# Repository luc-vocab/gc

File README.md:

Grind Control Device
====================

**2025/05/25 update: please see this new project https://github.com/LollosoSi/bruxism-detector**

**2015/10/01 update: I've started a new project, a wearable device focused on tracking sleep bruxism: 
 <a href="https://sleeptrack.io">SleepTrack</a>**

<b>Disclaimer: use this design, or any of the parts at your own risk.</b>

This device attemps to prevent night-time bruxism. It works by detecting muscle activation on the temporalis 
muscle and will emit an audio signal to wake the user up if bruxism is detected.

Features:
* Has an audio jack to plug-in headphones. These headphones are use to play an audio tone that will wake up the user during sleep if grinding is detected.
* An [EMG circuit](http://www.advancertechnologies.com/) is used along with custom-made electrodes that are placed on the temporalis muscle.
* A micro-SD card is used to record bruxism patterns for later analysis.
* A custom-made case was designed which can be 3d-printed.

The design is heavily inspired by the commercially available [Grind Care](http://grindcare.com/) device (which appears to no longer be available), except an audio signal is used instead of electrical impulses.

Do you have questions ? You may want to read all of the info below. You can also [contact me](mailto:grindcontrol@mailc.net)

Similar Projects
----------------
* Peter is planning on launching a commercial device, called Grindbit http://grindbit.launchrock.com/ - http://community.particle.io/t/im-building-a-night-time-bruxism-sleep-tracking-wearable-device/16840/6?u=dustpuppy
* Anthony is building a similar device, using a LIPO battery, an OLED display, SRAM chips http://chompr.blogspot.com
* Frank is starting on a similar project http://forums.adafruit.com/viewtopic.php?f=8&t=25611
* Lucy built a device using the EMG sensor and wrote a research paper http://lucyaimeemorcos.wordpress.com/2013/12/17/dont-grind-your-gears-pictures/
* Anthony setup a mailing list to discuss bruxism detection / prevention projects: https://groups.google.com/d/forum/bruxhackers

Photos
======

The device is worn around the neck, held by a strap:

Three electrodes are stuck on the temporalis muscle, the red one on the middle of the muscle, the blue one at the end, and the black one at a neutral area of the skin. Earphones are used for the audio signal:

The device with strap, earphone, and electrode cable. The case is a custom designed enclosure, designed in Sketchup and printed using Selective Laser Sintering:

Inside of the device, with two 9V batteries:

The printed circuit board. You can see the Arduino Micro microcontroller, micro-sd card reader, muscle sensor, switches and 3.5mm headphone jack.

The printed circuit board, designed in Eagle:

Schematics in Eagle:

Parts List
==========
* **Adafruit Arduino Micro** https://www.adafruit.com/products/1086
* **Adafruit MicroSD breakout board** https://www.adafruit.com/products/254
* **Advancer Technologies Muscle Sensor V3** http://www.advancertechnologies.com/p/muscle-sensor-v3.html
  * Also comes with electrodes
* **SS12SDH2 switch** http://www.mouser.hk/Search/ProductDetail.aspx?R=SS12SDH2virtualkey63300000virtualkey633-SS12SDH2
  * this switch is used to register an alarm / cancel the permanent alarm once it goes off.
* **SS22SDH2 switch** http://www.mouser.hk/Search/ProductDetail.aspx?R=SS22SDH2virtualkey63300000virtualkey633-SS22SDH2
  * this switch is used to power on the device. It simultaneously connects the two batteries.
* **66WR1KLF potentiometer / trimmer resistor** http://www.mouser.hk/Search/ProductDetail.aspx?R=66WR1KLFvirtualkey57700000virtualkey858-66WR1KLF
  * used to control the volume in the headphones
* **35RAPC2BV4 3.5mm headphone jack** http://www.mouser.hk/Search/ProductDetail.aspx?R=35RAPC2BV4virtualkey50210000virtualkey502-35RAPC2BV4
  * for audio output into headphones
* **10k ohm resistor**, a standard resistor will do.
* **MicroSD card** any capacity will do, the device usually outputs a 1mb file per night
* **MicroSD card reader** the data has to be analyzed on your computer using a card reader
* **Printed Circuit Board**, designed in Eagle CAD and printed using http://www.seeedstudio.com (https://github.com/lucwastiaux/gc/tree/master/gc1_eagle_project)
* **3d-printed case** printed using http://www.sculpteo.com, white SLS print (https://github.com/lucwastiaux/gc/tree/master/case)
* **9V batteries** http://www.amazon.com/gp/product/B0051WZ516 , these need to have enough capacity to last a whole night, the 550mah seem to last through a whole 10hr night. 
  * order enough of them as they are completely drained after one night
* **9V battery charger** http://www.amazon.com/gp/product/B005PUZQ04
* **2x 9V connectors + wires*** any electronics stores will have those
* **Rubber band** to hold the case together
* **Shure SE215 headphones** http://www.shure.com/americas/products/earphones/se-earphones/se215-sound-isolating-earphones
  * in-ear headphones with decent volume, and stay inside the ears the whole night.
* **Strapworks 1" tubular polyester webbing, 2 ft** http://www.strapworks.com/product_p/stpw1.htm
  * this is the hollow nylon strap used to wrap the headphone cable, electrode cable, and support strap
* **Strapworks 3/4" 4ft adjustable strap** http://www.strapworks.com/Strap_Adjuster_Straps_p/sas34l.htm
  * support strap to hold the device around the neck
 
Building
========

PCB
---
The PCB can be order on http://www.seeedstudio.com/. Select **Fusion PCB** service 
* PCB Qty. - 5 ( you can order more if you want to play around but the minimum is 5)
* Layer - 2
* PCB Thickness - 1.6mm
* PCB Dimension - 10cm Max*10cm Max
* PCB Color - Green
* Surface Finish - Hasl
* E-Test - 100% E-test(Free)

Submit the following zip file: https://github.com/lucwastiaux/gc/blob/master/gc1_eagle_project/gerber/gc1_20130428.zip

This should get you the exact same PCB that I have on my device without requiring processing in Eagle CAD. You will have 5 PCBs, and I recommend dedicating one for testing. You can solder male/female headers on that one to easily add/remove the Arduino, microSD breakout, and muscle sensor (other components like switches, you can just order extra and solder them on directly).

History and development
=======================

Symptoms and Diagnosis
----------------------
In October 2010, I started experiencing an unexplained permanent dizziness. It would come and go and be more severe 
during certain weeks. By March 2011, the symptoms had become more severe and included permanent headaches and facial
muscle pain. I started making doctor's appointments, saw three neurologists, one ENT doctor, took blood samples, had an
MRI brain scan but no diagnosis yet. Since the beginning I had been researching an explanation for those symptoms on the
web. Many leads did not pan out but I read that night-time bruxism (unconscious grinding of teeth at night-time) could
be a possible explanations. Several things pointed in that direction:
* I had been told before that I grind my teeth at night.
* My symptoms started one month after the end of an orthodontic treatment. After my orthodontic appliance was removed, I had to wear an Invisalign appliance, which is a transparent plastic mold designed to keep your teeth in place.
* Very quickly after starting to wear the Invisalign appliance, it started to show wear marks at the points of contact of my teeth.

I made an appointment with a New York dentist who made a special mouth guard designed to fit on the front teeth only.
This had a hugely positive impact on my symptoms and two months after wearing that, I believed the problem was gone.

However I occasionally still felt dizziness. In October of 2011, I had ocasional dizziness and semi-permanent headaches again.
This time, I experienced pain when chewing which clearly pointed to an issue with the jaw and especially jaw muscles.
In march 2012, I went to see a dentist in Hong Kong who made another type of mouthguard, and eventually put tooth fillings on my back teeth
to attempt to remediate a malocclusion problem. This had a beneficial impact. The dentist mentioned that night-time
bruxism is extremely challenging to control, that it may be caused by stress, but may become habitual and persist even
after the stress stimulus is removed.

In September 2012, I purchased the Grind Care device which detects night-time bruxism and attemps to condition you out of 
it by triggering a small electric shock. It's a very well made very compact device which you wear at night around your neck.
At electrode is stuck on your face near the temporal muscle. The electrode serves both to monitor muscle activity and
send a shock if muscle contraction is detected.

The grindcare device was the thing that helped me the most up to that point. It would give me some metrics of how many times
I ground my teeth at night. It started out at 140/night, then progressively moved to 30/night. My symptoms improved radically.
However by December 2012 the number of grinds/night started increasing, to 100/night, 200/night and even as high as 300/night
, as if my body had somehow adjusted and no longer cared about the electric shock.

The idea started forming in my head that the device should not just send an electric shock, but actually wake me up if 
bruxism is detected.

Development of Grind Control Device
-----------------------------------

In December 2012, I purchased a book on electronics to refresh my knowledge on the topic and learn some of the necessary
techniques such as soldering. I experimented with an USB voltmeter capable of detecting +/- 200mV. I started experimenting
with Operational Amplifiers. However in order to accurately detect muscle activity, you need a true EMG signal processing circuit.
I purchased an Olimex EMG and Arduino kit. That kit turned out not to be sensitive enough to detect temporal muscle activity.
A couple of weeks later, I received my Advancer Technologies Muscle Sensor v3. Through playing around with the electrodes
connected on my face, and measuring output voltage with a multimeter, I realized this was the way to go. The output voltage would
show 0.1V with muscles relaxed, and +0.9V with muscles contracted. This was perfect and exactly within the range that I needed
to process the signal with my Arduino Micro.

I needed some other parts in addition to the EMG sensor and Arduino Micro. In order to study grinding patterns, I needed
to record data and hence got the Adafruit microSD adapter. The programming is quite simple if you follow instructions. I also
needed an audio output. The arduino can output a square wave using the PWM output which is loud enough to wake you up. Using
a trimmer/potentiometer, I can control the volume. I needed a 3.5mm audio jack, some switches to turn the device on/off, and
one "control" switch.

My first prototype was made using an Adafruit perma-proto board. It's a PCB with a breadboard-like layout. I moved my parts
on there and connected them using solid core wire, soldered the whole thing together and cut off part of the board with shears.

I bought an enclosure which was the right size and had 2 9V battery compartments. The whole thing was quite bulky but it was ready
to use. I could then start working on the detection algorithm.

Later, I learned how to design PCBs in eagle and designed the layout you see above. It took me a couple of tries before getting
it right. Once I had the PCB and all components soldered on, I learned 3d modelling with Sketchup. Designed a case that
would fit 2 9V batteries, the PCB, and would have openings for the switches and connectors. That was a surprisingly easy
part of the process. The case is 3d-printed using Selective Laser Sintering.

Algorithm
---------

Once I had the final prototype ready, I started on fine-tuning my algorithm. I analyzed the data on the micro-sd card using
python scripts. Every morning, i would wake up and try to detect grinding patterns. The baseline output value from the EMG sensor
would be around 30 in general with no activity. When contracting the muscle, it would go up to 150-200. Sometimes it would stay 
at those high values for minutes during the night, about 1-2 hours after falling asleep. Detecting this high activity was easy,
but there were also times where I would see high values, low values alternating but it clearly didn't look like my jaw was 
at rest during that time. The tradeoffs were, I could set up the algorithm to be very sensitive, but there was a higher
risk of being woken up on a false alarm. Or I could set it up to be more permissive, and I would be unable to detect
certain grinding patterns and not fully solve the problem.

I experimented with many algoritms and ended up settling on a relatively easy one: count the number of "high"
values over the last 10 seconds (sampling 4 times per second). If they exceed 5, go into "alert 1" state, and issue an audio
beep with every new high value. Once the number of high readings exceed 10, issue a higher pitched beep with every new high value.
If they exceed 15, then go into alarm mode and continuously beep until the user resets the device.

Notes about using Arduino Micro
-------------------------------

Working with the Arduino Micro was a good experience overall. The only issue is the limited amount of RAM: 2.5kb. This
is very restrictive. The most annoying issue is that the device will automatically reset if you run out of RAM. It took
me a long time to understand that. Other than that, the Arduino is perfect for this application. The power consumption is
such that I'll go through 2 500mah 9V batteries in one night. Not a big deal since I can recharge them easily.

Experiences using the device
============================

For many months I had grown convinced that the source for my issues is an unconscious night-time behavior of my jaw that 
no one could explain. It seemed obvious to me that if I could detect this and stop it then I would solve my problem.
To me this has been a very successful project. Since I started using the device in April 2013, my symptoms have improved
progressively but very noticeably.

The first times I got woken up by the beeping audio sound were a victory for me as I had finally found an effective
system to put a stop to this destructive unconscious habit. I distintively remember being woken up a few times with 
my jaw clenched and the device beeping into my ears. I had no idea why my jaw was clenched but only after I became more
conscious would I relax my jaw muscles. This was a revelation and yet another proof that my problems were due to night-time,
unconscious bruxism.

There are some drawbacks, the biggest one being interference with your sleep. In my case, it was a lot better to interrupt
my sleep than to let the destructive night-time bruxism keep on happening. However sleep segmentation may have some negative side
effects. Ironically, sleep deprivation may lead to headaches so you need to be careful if you try something like that.

One source of frustration is that bruxism is not well understood by the medical community. Most doctors and dentist will
not be able to help you much besides suggesting mouth guards and other dental treatments. There is a belief that bruxism
is caused by malocclusion or other problems in the mouth. While that may be true, i've also heard dentists say that you could
have perfect teeth and still experience bruxism symptoms. Other people will say it's due to stress. In my personal opinion,
bruxism becomes a habit that is very hard to get rid of. While it may initially be due to stress or dental problems, it will
become a habit that you cannot control.

I now no longer wear the device regularly as my symptoms have improved significantly. I will occasionally wear it if I feel
symptoms coming back. But judging by the last 2 months, it seems like it is possible to have a lasting improvement.

Problems with current design
----------------------------
* No LCD screen. This makes it difficult to experiment with different algorithms as you can't tell what the current reading is.
* Only works off 9V batteries. I end up having to charge a new set every day.
* The sensitivity is based on the EMG readings from my muscles. It may vary from one person to another. Right now the only way to change this is in the code.

Potential improvements
----------------------
* Add small LCD screen to show current readings and accumulated high-readings. This will be useful if the device starts beeping in the middle of the night and you don't know why.
* Add some buttons to configure sensitivity. This would allow a new user to use the device without programming.
* As an alternative to the above, I could use a Low-Energy Bluetooth chip and control the whole thing from an iPhone or Android phone. I have
 no experience with that, but it's an interesting idea. Not sure what it would mean for power consumption, although with on-board storage, I wouldn't need
to keep the bluetooth radio on the whole night, only when the user is configuring the device.
* Run off a LIPO battery. This presents some challenges, as the EMG sensor requires a dual power supply, and with the 2 9V batteries forming a +/- 9V dual supply, the output voltage 
of the EMG sensor moves between 0.1V and 0.9V. This is only a small range of the Arduino's 0V-5V resolution. Maybe my mucles are weak. If I were to use a LIPO battery, I would
have to first use a step-up converter to increase the voltage from 3.7V to 9V, and then create a dual power supply. This is beyond my level of knowledge. There are some ready-made boost
converters you can buy, I may look into those. Then I may need a charging circuit for the LIPO, but again that's beyond my area of expertise.

Interested in using this ?
==========================

In its current state, I cannot recommend using this device to anyone who is not an engineer. You may have to do a lot of 
experimentation to get it work for you, however if your bruxism symptoms are as severe as mine were, I can only encourage 
you to pursue this. I'm not planning on making an updated version right now, but several people have expressed interest.
If you have any ideas around this please contact me.

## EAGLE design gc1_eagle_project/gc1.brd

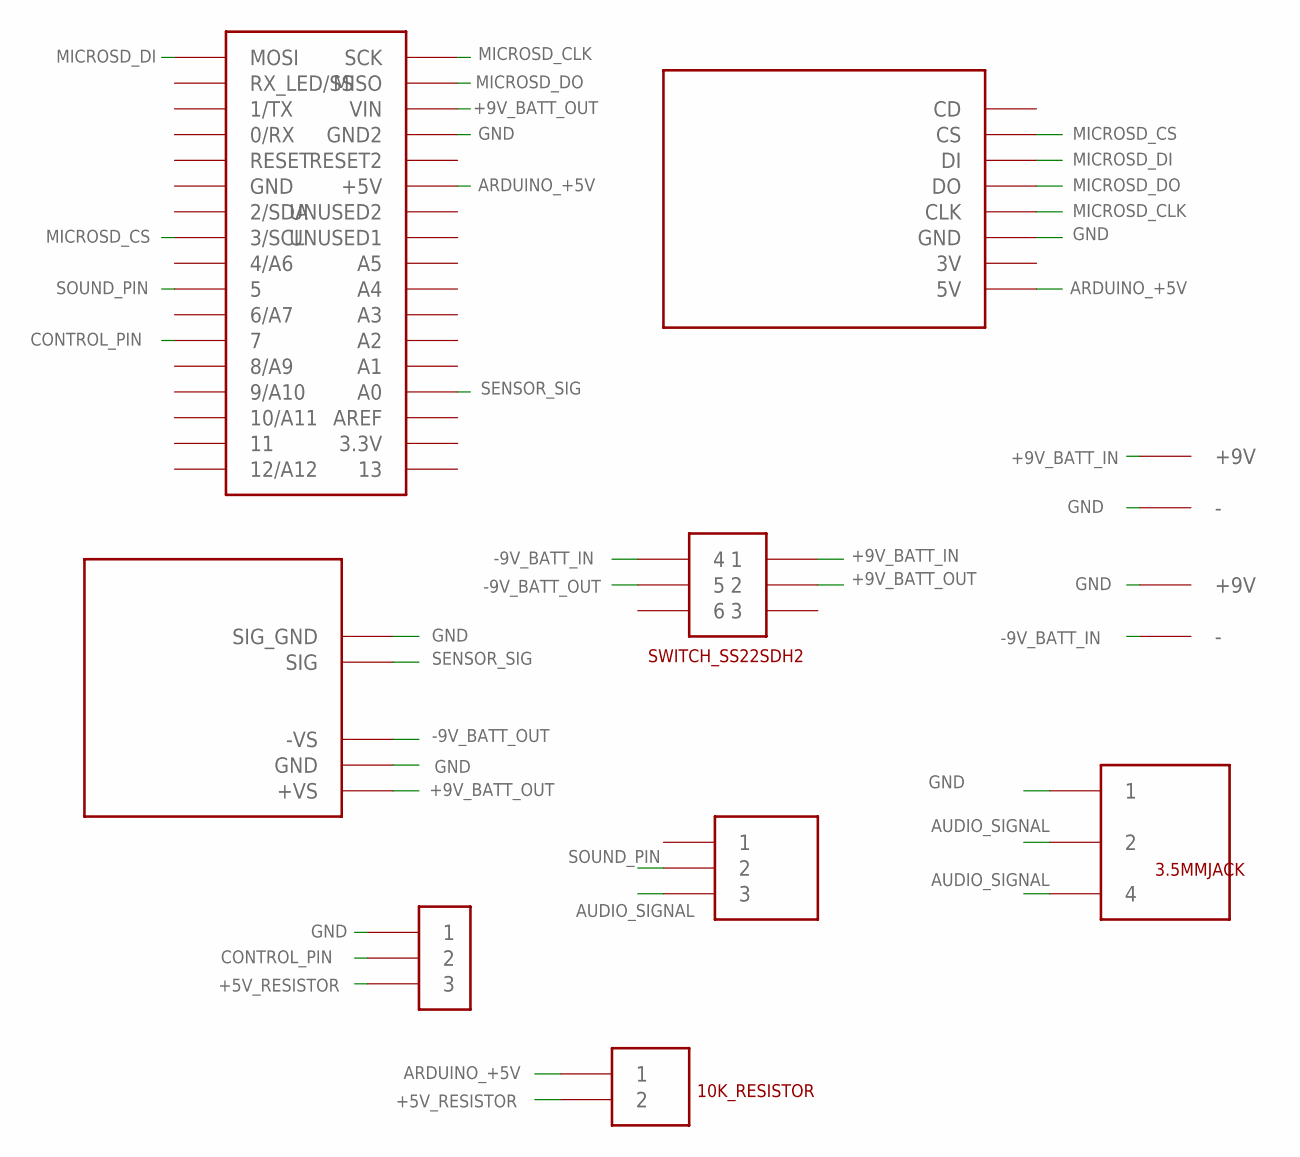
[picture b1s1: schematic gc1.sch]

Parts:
3.5MMJACK: 35RAPC2BVN4; 35RAPC4BVN4
10K_RESISTOR: 10K_RESISTOR
ARDUINOMICRO: ARDUINO_MICRO
TRIMMER: 66WR1KLF
U$2: MICROSD
U$3: MUSCLE_SENSOR
U$4: SWITCH_SS22SDH2
U$5, U$6: 9V_CONNECTOR
U$9: SWITCH_SS12SDH2

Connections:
+5V_RESISTOR: 10K_RESISTOR.2, U$9.3
+9V_BATT_IN: U$4.1, U$5.+9V
+9V_BATT_OUT: ARDUINOMICRO.VIN, U$3.+VS, U$4.2
-9V_BATT_IN: U$4.4, U$6.-
-9V_BATT_OUT: U$3.-VS, U$4.5
ARDUINO_+5V: 10K_RESISTOR.1, ARDUINOMICRO.+5V, U$2.5V
AUDIO_SIGNAL: 3.5MMJACK.2, 3.5MMJACK.4, TRIMMER.3
CONTROL_PIN: ARDUINOMICRO.7, U$9.2
GND: 3.5MMJACK.1, ARDUINOMICRO.GND2, U$2.GND, U$3.GND, U$3.SIG_GND, U$5.-, U$6.+9V, U$9.1
MICROSD_CLK: ARDUINOMICRO.SCK, U$2.CLK
MICROSD_CS: ARDUINOMICRO.3/SCL, U$2.CS
MICROSD_DI: ARDUINOMICRO.MOSI, U$2.DI
MICROSD_DO: ARDUINOMICRO.MISO, U$2.DO
SENSOR_SIG: ARDUINOMICRO.A0, U$3.SIG
SOUND_PIN: ARDUINOMICRO.5, TRIMMER.2

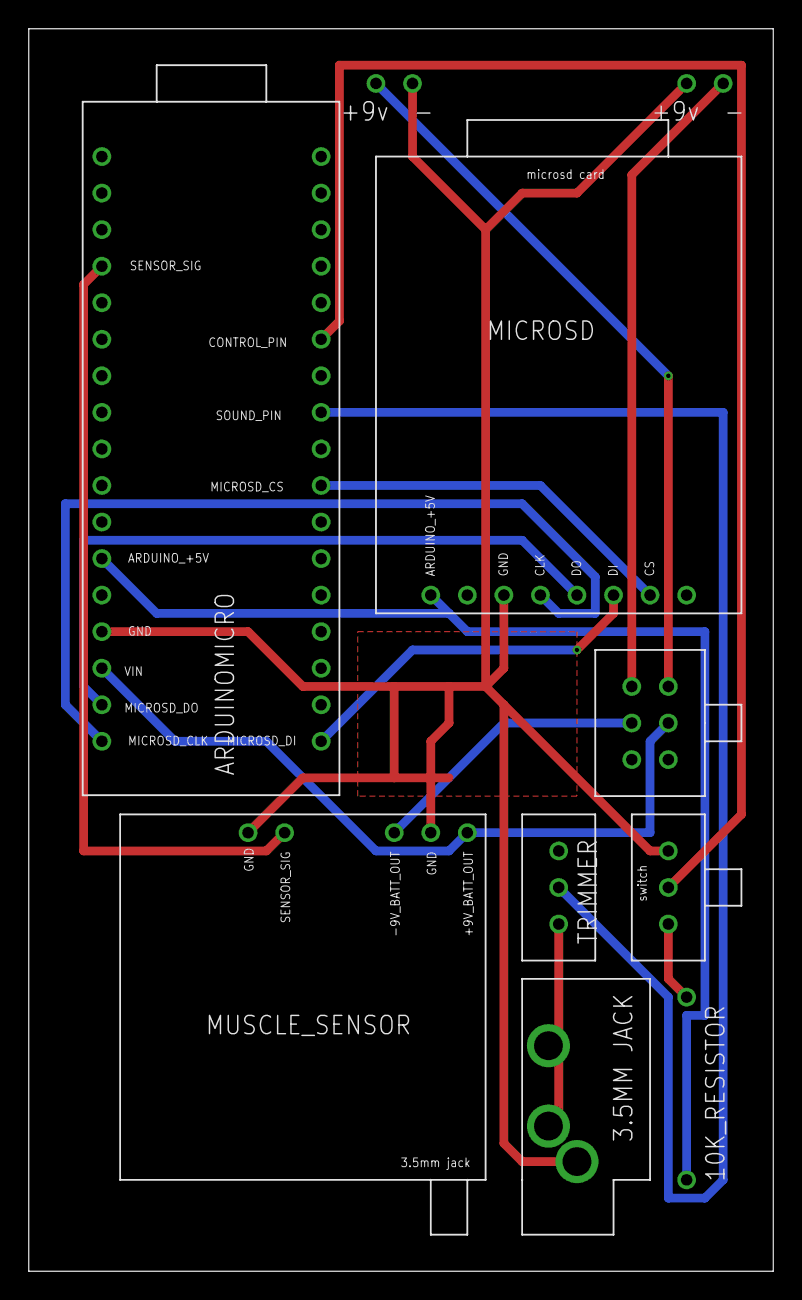
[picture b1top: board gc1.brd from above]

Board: 2 copper layers, 51.7 x 86.4 mm, 10 parts (0 on the bottom side), 15 nets.

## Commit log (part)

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2016-01-17 add log_base function
2016-01-17 remove verbose logging level
2016-01-17 indicate when loading data
2016-01-17 log owner_uid in server, exit test client when done
2016-01-17 support letsencrypt certificate
2016-01-17 allow fetching cloudinary logo over http
2016-01-17 fix image link
2016-01-17 force loading image over https
2016-01-23 server debugging, allow loading multiple gc1 data files, add underscore library
2016-01-23 send confirmation byte after initial handshake
2016-01-23 integrate smoothie charts to show historical emg data
2016-01-23 show min and max values
2016-01-24 disable simulation mode
2016-01-24 report battery level every 2mn
2016-01-26 device monitor to figure out whether device is online or not
2016-01-26 add additional device states, manage routes for control better
2016-01-26 indicate whether device is in realtime mode, don't query influx db unless device is in night mode
2016-01-29 use FB_ROOT as input to gulp config generation
2016-01-30 refactor server code, introduce config class
2016-01-30 use proper environment key in influxdb tags
2016-01-30 remove unneeded config
2016-01-30 add basic docker file
2016-01-30 use common launcher for both servers
2016-01-30 fix selecting different server
2016-01-30 use angular.element instead of jquery
2016-01-30 initial import
2016-01-30 changed date
2016-01-30 include excerpt
2016-01-31 adding necessary css/js files for jekyll
2016-01-31 Housekeeping
    - Removed log files and other misc junk files/
    - uploaded assembly photos for V1
2016-01-31 include font-awesome, add menu entries
2016-01-31 add blog landing page
2016-02-04 remove simple line icons
2016-02-05 remove default sass code, add color function
2016-02-06 moved project status into include file
2016-02-06 fixed update date css
2016-02-06 add blog-specific layout
2016-02-06 adding images
2016-02-06 added more images
2016-02-07 new device article
2016-02-07 add previous/next articles
2016-02-07 improve responisiveness of prev/next articles
2016-02-07 use logo on blog index
2016-02-07 only add padding above a certain width
2016-02-07 use full width below a certain screen size
2016-02-07 use https urls everywhere
2016-02-07 add separate directory for firebase.json for website
2016-02-07 change layout of prev/next post links
2016-02-07 add contact page
2016-02-07 fixed a few links
2016-02-07 added mailmunch form
2016-02-08 sleeptrack link
2016-02-08 fix typo
2016-02-08 put together haptic motor driver test
2016-02-09 change image links to https
2016-02-09 fixed link error
2016-02-14 renamed index.html file, removed assets
2016-02-14 change destination
2016-02-14 build blog on changes
2016-02-14 add fonts back in
2016-02-14 remove spaces in css and js statements
2016-02-14 use absolute path in useref tag
2016-02-14 build blog on gulp build task, put jekyll tasks in separate script
2016-02-14 working redirection to clean urls
2016-02-14 also try adding .html extension to files
2016-02-14 move app.html to app/index.html during inject task
2016-02-14 serve static assets dir as well in dev
2016-02-14 remove blog_site on clean
2016-02-15 add common header sass file
2016-02-15 watch common sass area when building. add padding on either side in mobile mode
2016-02-15 remove pubnub
2016-02-20 in dev mode, generate blog with drafts
2016-02-20 added paragraph about sleepguard advantages
2016-02-21 use new keyword to instantiate new GcInfluxData
2016-02-21 use user_name instead of device_name, as that's the key under which influxdb data gets inserted
2016-02-23 add environment
2016-02-23 add task to copy misc blog files such as feed.xml
2016-02-23 wrote some more on bruxism devices, added email include
2016-02-23 fixed grindcare link
2016-02-23 moved bruxism devices article, added image include
2016-02-23 move google analytics tracker to head
2016-02-25 added two devices
2016-02-27 instantiate device monitor with new
2016-02-27 properly reject promise when saving of settings fails
2016-02-27 watch for changes in user's device_id and update subscription accordingly
2016-02-27 properly show status if no device is configured
2016-02-27 set server key if user already selected one
2016-02-27 show min and max for the 30s and 5s windows
2016-02-27 calculate avg for both time horizons
2016-02-27 imu specs first draft
2016-02-27 first import
2016-02-27 questions
2016-02-27 connector question
2016-02-29 External IMU Board added
    - Updated artwork (Sleeptrack V2 Final)
    -Created IMU External PCB and Schematic
2016-03-01 IMU External PCB Single Sided
    -compressed board to single sided.
    -still need to edit silkscreen and finalize the schematic.
2016-03-02 IMU External
    - Added BOM V1
2016-03-04 IMU External
    -Fixed issue where the copper was not exposed on 0402 components.
    -updated artwork, brd, and schematic pdfs.
2016-03-10 remove simulation mode, change data collection frequency to be slower in realtime mode
2016-03-10 bruxism and rhodiola article
2016-03-10 various edits on magnesium article
2016-03-11 change current status
2016-03-12 bno055 test
2016-03-20 initial myoware model
2016-03-20 added pegs
2016-03-20 few problems left to fix
2016-03-20 sketchup model with only myoware cover
2016-03-20 fixed internal faces in model
2016-03-20 add two more versions
2016-03-21 Housekeeping and documentation updates
    -Added new PDF folder to store Schematic and PCB PDF's
    -cleaned up root
2016-03-21 SleepTrack V3 and IMU External V2 Artwork Generated
    Fixed outstanding issues with the boards and regenerated artwork and
    drill files.
2016-03-21 initial commit of mouthguard bruxism article
2016-03-21 change link to https
2016-03-23 Timesheet 7
    Updated timesheet for 2/29/16-3/22/16
2016-03-24 simulation mode can be toggled
2016-03-24 toggle EMG beep on / off
2016-03-24 remove other gauges
2016-03-25 mark server as connected when reconnection happens
2016-03-25 resize smoothie chart if window in narrow, after taking into account margin
2016-03-25 disable google analytics for anything but prod domain
2016-03-27 elecrow instructions
2016-03-28 SleepTrack V3 Artwork Rev B
    -Updated Artwork to connect USB pin 5 to GND instead of Dummy NEt
    -Removed Vout+ and NC trace
    -Regenerated manufacture files and PDFs
2016-03-30 BRD Git Test
2016-04-09 new article
2016-04-09 added images
2016-04-14 initial commit of first article
2016-04-14 added thumbnails, more paragraphs
2016-04-14 added feaetures left to do
2016-04-15 further clarifications
2016-04-22 Added new circuit components
    -Haptic Feedback
    - BNO055 IMU
2016-04-30 first import of tmj article
2016-05-01 removed unneeded pages, added twitter and facebook contacts
2016-05-01 updated current status (rev 3 of pcb)
2016-05-01 added RSS link
2016-05-01 correctly use active link for blog home
2016-05-04 added components
2016-05-04 pin markings
2016-05-04 added LM3914
2016-05-07 proposed sleeptrack2 design phases
2016-05-07 changed headers
2016-05-07 expose pins with through-holes
2016-05-16 Breakout Board V1
    -Completed Breakout board pcb
    -generated artwork
    - exported pdfs of schematic and pcb
2016-05-16 a few mentions about the circuit
2016-05-21 Directory Change
    -moved all versions of Sleeptrack and Add on boards to Projects Folder
2016-05-30 LM3914 datasheet
2016-05-30 use adafruit BNO055 circuit
2016-06-02 Sleeptrack2_Phase 1 Board Geometry updated
    -added 3 mounting holes (4-40 screw size)
    - filleted corners
2016-06-10 Sleeptrack2_Phase 1
    Final Board Artwork V1
2016-06-10 Revert "Sleeptrack2_Phase 1"
    This reverts commit 92b435aabf790c8d8d8b8fd82f348b68dcef08d7.
2016-06-11 changed phase 2 to include only BNO055
2016-06-11 no need for level switching
2016-06-18 added BNO055 datasheet
2016-06-28 publish charge to particle cloud
2016-07-01 selectable use in IMU in main firmware, publish values on particle cloud in bno055 example
2016-07-01 initial version with texture of board
2016-07-01 working flat board with all component heights
2016-07-01 finished 3d model of case
2016-07-02 initial import of phase1 case
2016-07-02 case and battery space
2016-07-02 finalized top and bottom parts
2016-07-02 working top and bottom cases
2016-07-02 final checkin
2016-07-09 article text
2016-07-09 updated status
2016-07-10 don't attempt to read from IMU if IMU is disabled
2016-07-15 Sleeptrack2 Phase 2 V1
    -Finalized Schematic
    -Finalized PCB
    -Artwork created
    -Drill Files
    -PDF of PCB and Schematic
    Sleeptrack Phase 2 Functions:
2016-07-20 Sleeptrack2_Phase2_v1
    Added BOM
2016-07-20 adding BNO055, speaker and buttons to wishlist for phase 3
2016-07-21 notes about speaker and button
2016-08-16 alter test_bno055 so that it doesn't timeout wifi/cloud
2016-08-19 Sleeptrack2_Phase 3
    -Breakout IMU Schematic added
2016-08-26 Phase 3 Layout/Route
    -Completed Layout/Route of Phase 3 PCB
    -Added Breakaway IMU with Molex Picolock connector
    -Added 2 PB Switches
    -Added Speaker
    -Utilized wasted space on breakaway peice to implement breakout board
    for bno055
2016-09-12 change permissions
2016-09-13 working compilation
2016-09-16 don't store data in eeprom
2016-09-20 Phase 3
    V1 commit
2016-09-25 working sleeptrack diagnostics firmware for speaker
2016-09-25 working streaming of battery state
2016-09-25 working sleeptrack diagnostics with bno055
2016-10-13 other wishes for phase 4, link to DRV2605 haptic driver
2016-10-15 duplicated bno055 test code
2016-10-15 add product version and product id
2016-10-15 make board smaler
2016-10-15 setup process
2016-10-15 flexible , grindcare
2016-10-16 show lag on realtime apge
2016-10-16 updated build script
2016-10-21 write additional timestamps during handshake
2016-10-21 fix cmd arguments
2016-10-21 install influxdb
2016-10-26 phase 4 more details
2016-10-26 imu details
2016-10-26 reformatted and added t-shaped connector
2016-10-27 added battery dimensions
2016-11-20 added note about photon through-holes
2016-11-26 add bno055 libraries
2016-11-26 removed libraries from the ignore file
2016-11-26 multiply accelerometer values by 1000 only
2016-11-26 transmit button state
2016-11-26 add lag check
2016-11-26 overlay on the chart whehter button is pressed or not
2016-11-26 fix conversion to G
2016-11-26 read taps
2016-11-29 use two different defines for both imus. integrate mma8452
2016-11-29 send accel from both IMUs to gc_client
2016-11-29 store accelerometers 2 values
2016-11-30 double tap to upload
2016-12-01 send linear acceleration only for bno055, and send raw int16_t values
2016-12-01 turn on wifi ahead of time, manage wifi within gc_client
2016-12-03 Phase 4
    altium project
2016-12-10 mention tempo automation
2016-12-11 update command line to run gc server
2016-12-11 detect fast movement
2016-12-11 disable tap to upload in realtime mode
2016-12-11 change bno055 fast movement threshold
2016-12-11 turn on and off fast movement
2016-12-11 read several flags in addition to the button flag
2016-12-11 rounded corners
2016-12-14 Phase 4 Almost done
    -loosley finalized component placement
    -Photon footprint updated
    -other board layout finalization.
2016-12-17 break out gyro values in all axes, remove emg value
2016-12-17 change structure alignment
2016-12-18 read stddev packets
2016-12-18 send stddev
2016-12-18 write data_type the proper way
2016-12-18 put writing to influxdb back in for data_point
2016-12-18 change name
2016-12-18 change back to debug
2016-12-18 only turn off led in night mode
2016-12-18 progress
2016-12-19 regroup stddev recordings under the same measurements
2016-12-19 added pictures
2016-12-20 changed current status
2016-12-29 Sleeptrack 4 and BNO055 Host Board
    -Production files and BOM
2017-01-29 added test motor cloud function
2017-01-29 update version to 3
2017-02-01 upgrade firebase sdk
2017-02-01 updated configs
2017-02-01 renamed functions to match sdk3
2017-02-01 commented out dead code
2017-02-01 upgraded gulp-minify-css
2017-02-01 add prod firebase config
2017-02-01 added dev and prod aliases
2017-02-04 ensure D4 is high in order to test motor driver
2017-02-10 adapt to firebase 3 sdk
2017-02-11 adding dev docker stack
2017-02-11 change startup command line
2017-02-11 gc server starting up
2017-02-11 more sdk3 updates
2017-02-11 added gc servers
2017-03-13 BNO055 Production files
